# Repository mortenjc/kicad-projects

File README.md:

# kicad-projects
Files for schematics and PCB layout

## retroclock

This project relates to the DCF77 decoder project found here

https://github.com/mortenjc/dcf77

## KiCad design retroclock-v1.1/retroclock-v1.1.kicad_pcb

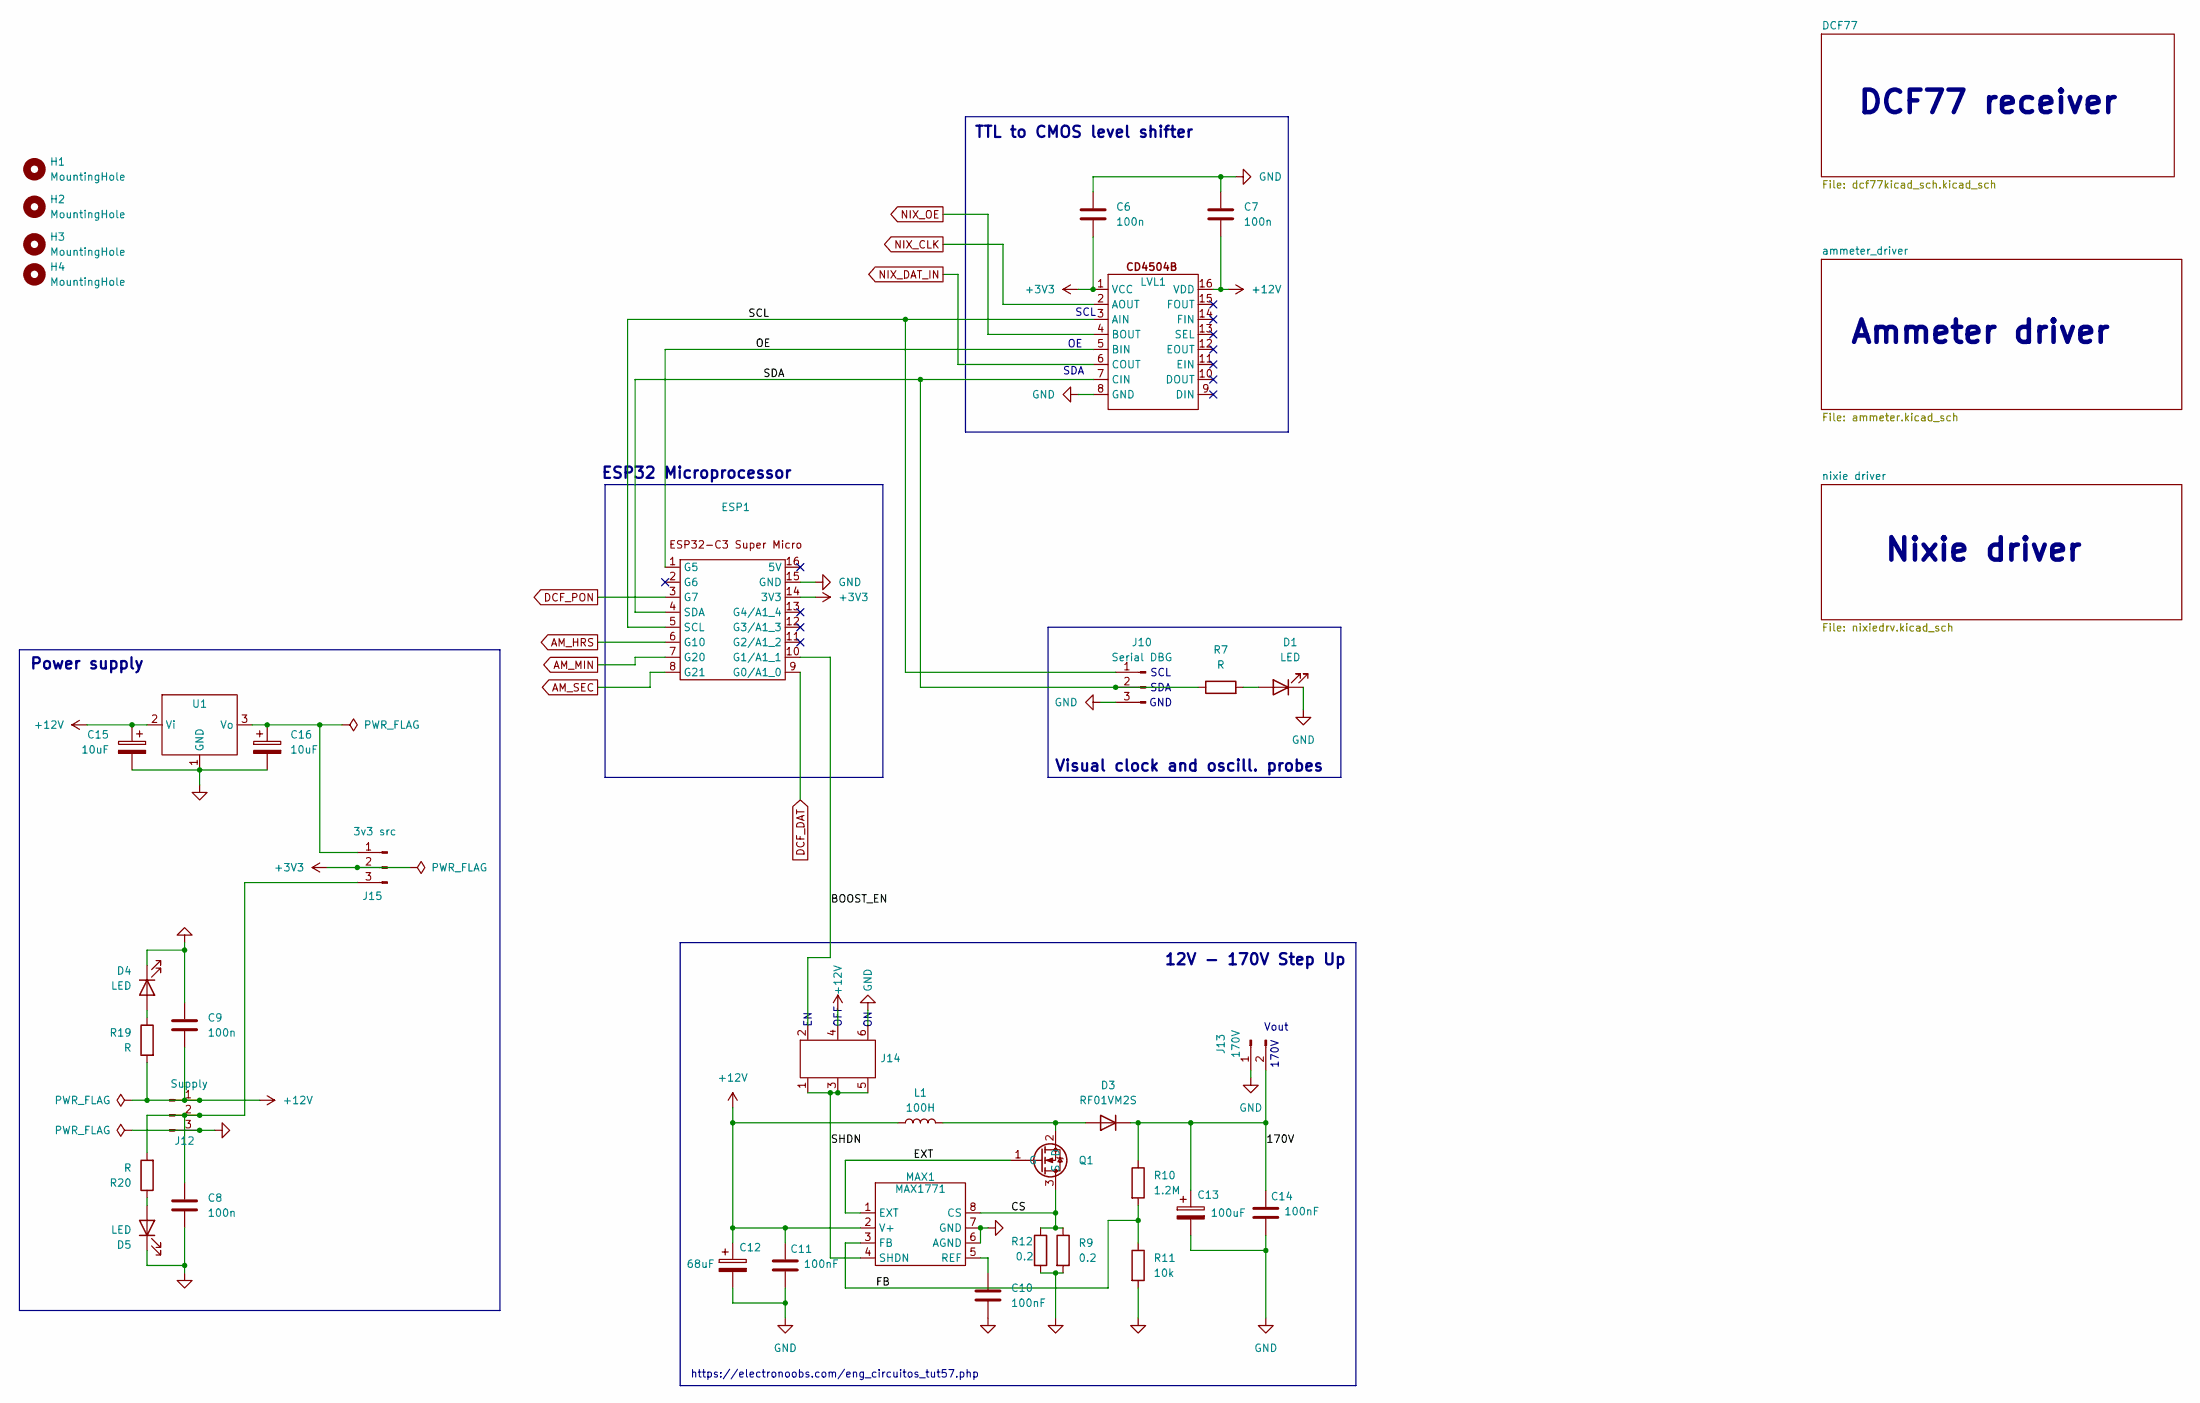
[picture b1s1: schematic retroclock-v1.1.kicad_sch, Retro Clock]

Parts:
C6, C8, C9: 100n; C_Disc_D3.4mm_W2.1mm_P2.50mm
C7: 100n; C_1206_3216Metric_Pad1.33x1.80mm_HandSolder
C10, C11: 100nF; C_Disc_D3.4mm_W2.1mm_P2.50mm
C12: 68uF; CP_Radial_D8.0mm_P3.80mm
C13: 100uF; CP_Radial_D10.0mm_P5.00mm
C14: 100nF; C_Rect_L18.0mm_W7.0mm_P15.00mm_FKS3_FKP3
C15, C16: 10uF; CP_Radial_D8.0mm_P3.80mm
D1, D4, D5: LED; LED_D3.0mm_Clear
D3: RF01VM2S; D_DO-15_P15.24mm_Horizontal
ESP1: ESP32 Header
H1, H2, H3, H4: MountingHole; MountingHole_2.2mm_M2_Pad
J10: Serial DBG; PinHeader_1x03_P2.54mm_Vertical
J12: Supply; Molex_KK-254_AE-6410-03A_1x03_P2.54mm_Vertical
J13: 170V; Molex_KK-254_AE-6410-02A_1x02_P2.54mm_Vertical
J14: Jumper 2.54 2x03
J15: 3v3 src; PinHeader_1x03_P2.54mm_Vertical
L1: 100H; L_Radial_D10.0mm_P5.00mm_Neosid_SD12k_style3
LVL1: SOIC-16_3.9x9.9mm_P1.27mm
MAX1: MAX1771; SOIC-8_3.9x4.9mm_P1.27mm
Q1: MOSFET
R7, R19, R20: R; R_Axial_DIN0204_L3.6mm_D1.6mm_P7.62mm_Horizontal
R9, R12: 0.2; R_Axial_DIN0204_L3.6mm_D1.6mm_P7.62mm_Horizontal
R10: 1.2M; R_Axial_DIN0204_L3.6mm_D1.6mm_P7.62mm_Horizontal
R11: 10k; R_Axial_DIN0204_L3.6mm_D1.6mm_P7.62mm_Horizontal
U1: HT7333

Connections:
+3V3: C6.2, ESP1.14 (3V3), J15.2, LVL1.1 (VCC); also elsewhere on the board
+12V: C7.1, C9.2, C11.1, C12.1, C15.1, J12.1, J14.4, L1.1, LVL1.16 (VDD), MAX1.2 (V+), R19.2, U1.2 (Vi); also elsewhere on the board
/170V: C13.1, C14.1, D3.1 (K), J13.2, R10.1
/BOOST_EN: ESP1.10 (G1/A1_1), J14.2
/CS: MAX1.8 (CS), Q1.3 (S), R9.1, R12.1
/EXT: MAX1.1 (EXT), Q1.1 (G)
/FB: MAX1.3 (FB), R10.2, R11.1
/OE: ESP1.1 (G5), LVL1.5 (BIN)
/SCL: ESP1.5 (SCL), J10.1, LVL1.3 (AIN)
/SDA: ESP1.4 (SDA), J10.2, LVL1.7 (CIN), R7.1
/SHDN: J14.1, J14.3, J14.5, MAX1.4 (SHDN)
AM_HRS: ESP1.6 (G10); also elsewhere on the board
AM_MIN: ESP1.7 (G20); also elsewhere on the board
AM_SEC: ESP1.8 (G21); also elsewhere on the board
DCF_DAT: ESP1.9 (G0/A1_0); also elsewhere on the board
DCF_PON: ESP1.3 (G7); also elsewhere on the board
GND: C6.1, C7.2, C8.2, C9.1, C10.2, C11.2, C12.2, C13.2, C14.2, C15.2, C16.2, D1.1 (K), D4.1 (K), D5.1 (K), ESP1.15 (GND), J10.3, J12.3, J13.1, J14.6, LVL1.8 (GND), MAX1.6 (AGND), MAX1.7 (GND), R9.2, R11.2, R12.2, U1.1 (GND); also elsewhere on the board
NIX_CLK: LVL1.2 (AOUT); also elsewhere on the board
NIX_DAT_IN: LVL1.6 (COUT); also elsewhere on the board
NIX_OE: LVL1.4 (BOUT); also elsewhere on the board
unnamed: D1.2 (A), R7.2
unnamed: D3.2 (A), L1.2, Q1.2 (D)
unnamed: D4.2 (A), R19.1
unnamed: D5.2 (A), R20.1
unnamed: C8.1, J12.2, J15.3, R20.2
unnamed: C16.1, J15.1, U1.3 (Vo)
unnamed: C10.1, MAX1.5 (REF)

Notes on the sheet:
https://electronoobs.com/eng_circuitos_tut57.php
ESP32 Microprocessor
Nixie driver
GND
SCL
OFF
Vout
Power supply
170V
Visual clock and oscill. probes
SDA
12V - 170V Step Up
DCF77 receiver
TTL to CMOS level shifter
Ammeter driver

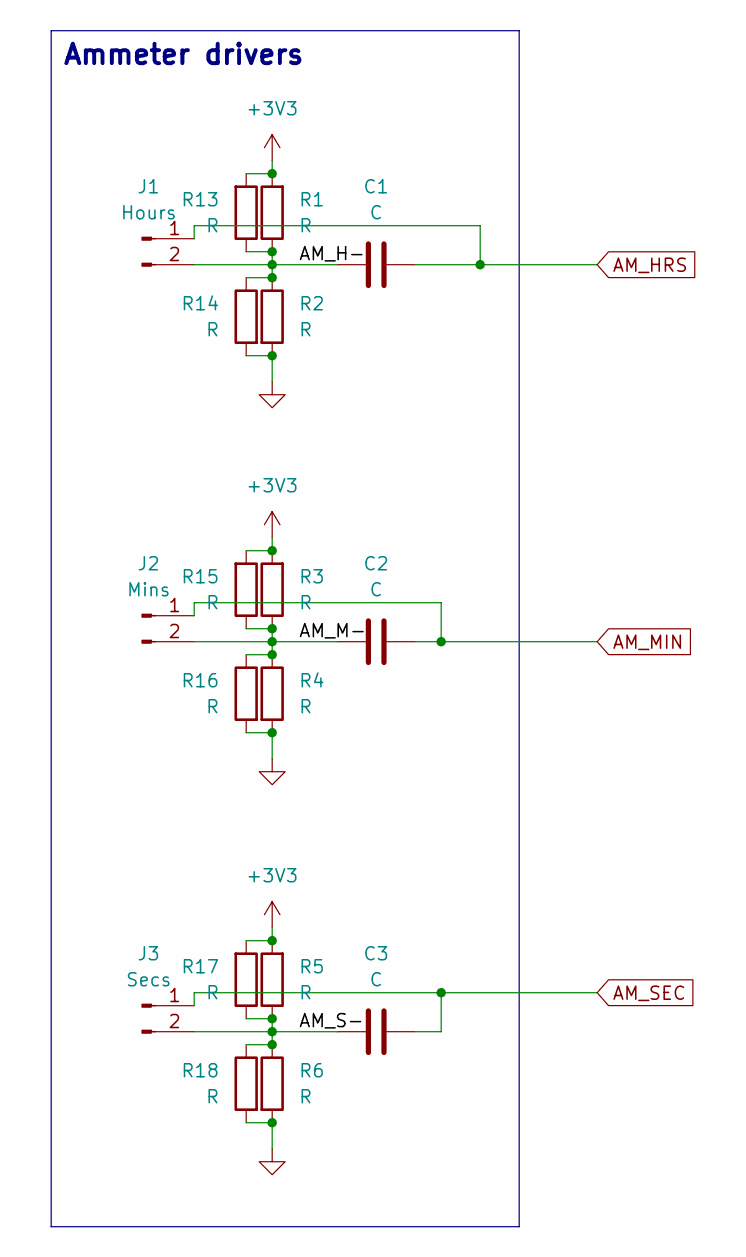
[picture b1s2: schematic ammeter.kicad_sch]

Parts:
C1, C2, C3: C; C_Axial_L19.0mm_D7.5mm_P25.00mm_Horizontal
J1: Hours; Molex_KK-254_AE-6410-02A_1x02_P2.54mm_Vertical
J2: Mins; Molex_KK-254_AE-6410-02A_1x02_P2.54mm_Vertical
J3: Secs; Molex_KK-254_AE-6410-02A_1x02_P2.54mm_Vertical
R1, R2, R3, R4, R5, R6, R13, R14, R15, R16, R17, R18: R; R_Axial_DIN0204_L3.6mm_D1.6mm_P7.62mm_Horizontal

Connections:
+3V3: R1.2, R3.2, R5.2, R13.2, R15.2, R17.2; also elsewhere on the board
/ammeter_driver/AM_H-: C1.2, J1.2, R1.1, R2.1, R13.1, R14.1
/ammeter_driver/AM_M-: C2.2, J2.2, R3.1, R4.1, R15.1, R16.1
/ammeter_driver/AM_S-: C3.2, J3.2, R5.1, R6.1, R17.1, R18.1
AM_HRS: C1.1, J1.1; also elsewhere on the board
AM_MIN: C2.1, J2.1; also elsewhere on the board
AM_SEC: C3.1, J3.1; also elsewhere on the board
GND: R2.2, R4.2, R6.2, R14.2, R16.2, R18.2; also elsewhere on the board

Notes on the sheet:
Ammeter drivers

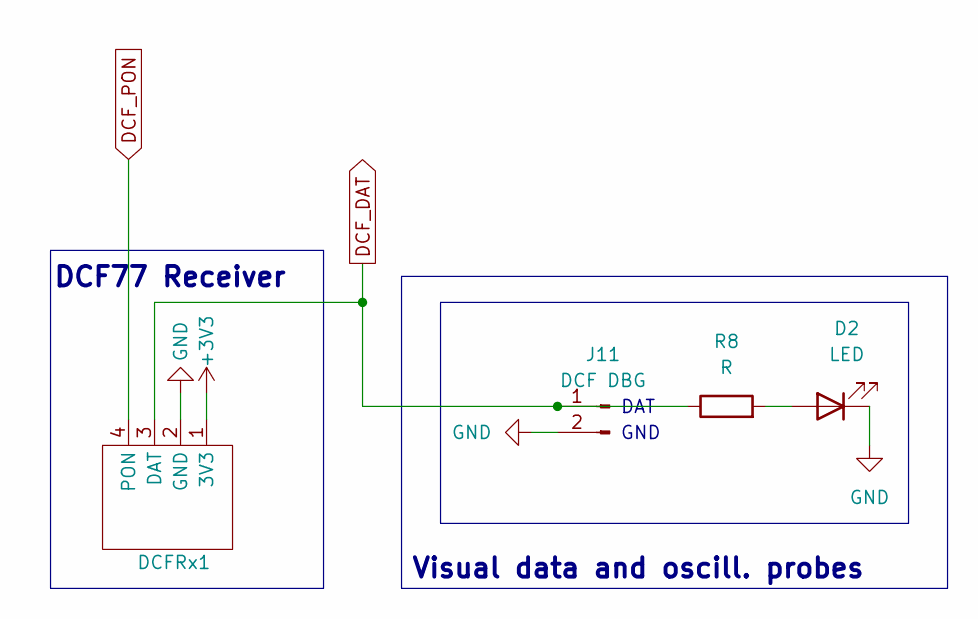
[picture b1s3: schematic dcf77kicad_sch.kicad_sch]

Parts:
D2: LED; LED_D3.0mm_Clear
DCFRx1: DCF77Rx_A
J11: DCF DBG; Molex_KK-254_AE-6410-02A_1x02_P2.54mm_Vertical
R8: R; R_Axial_DIN0204_L3.6mm_D1.6mm_P7.62mm_Horizontal

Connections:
+3V3: DCFRx1.1 (3V3); also elsewhere on the board
DCF_DAT: DCFRx1.3 (DAT), J11.1, R8.1; also elsewhere on the board
DCF_PON: DCFRx1.4 (PON); also elsewhere on the board
GND: D2.1 (K), DCFRx1.2 (GND), J11.2; also elsewhere on the board
unnamed: D2.2 (A), R8.2

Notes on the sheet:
GND
DAT
DCF77 Receiver
Visual data and oscill. probes

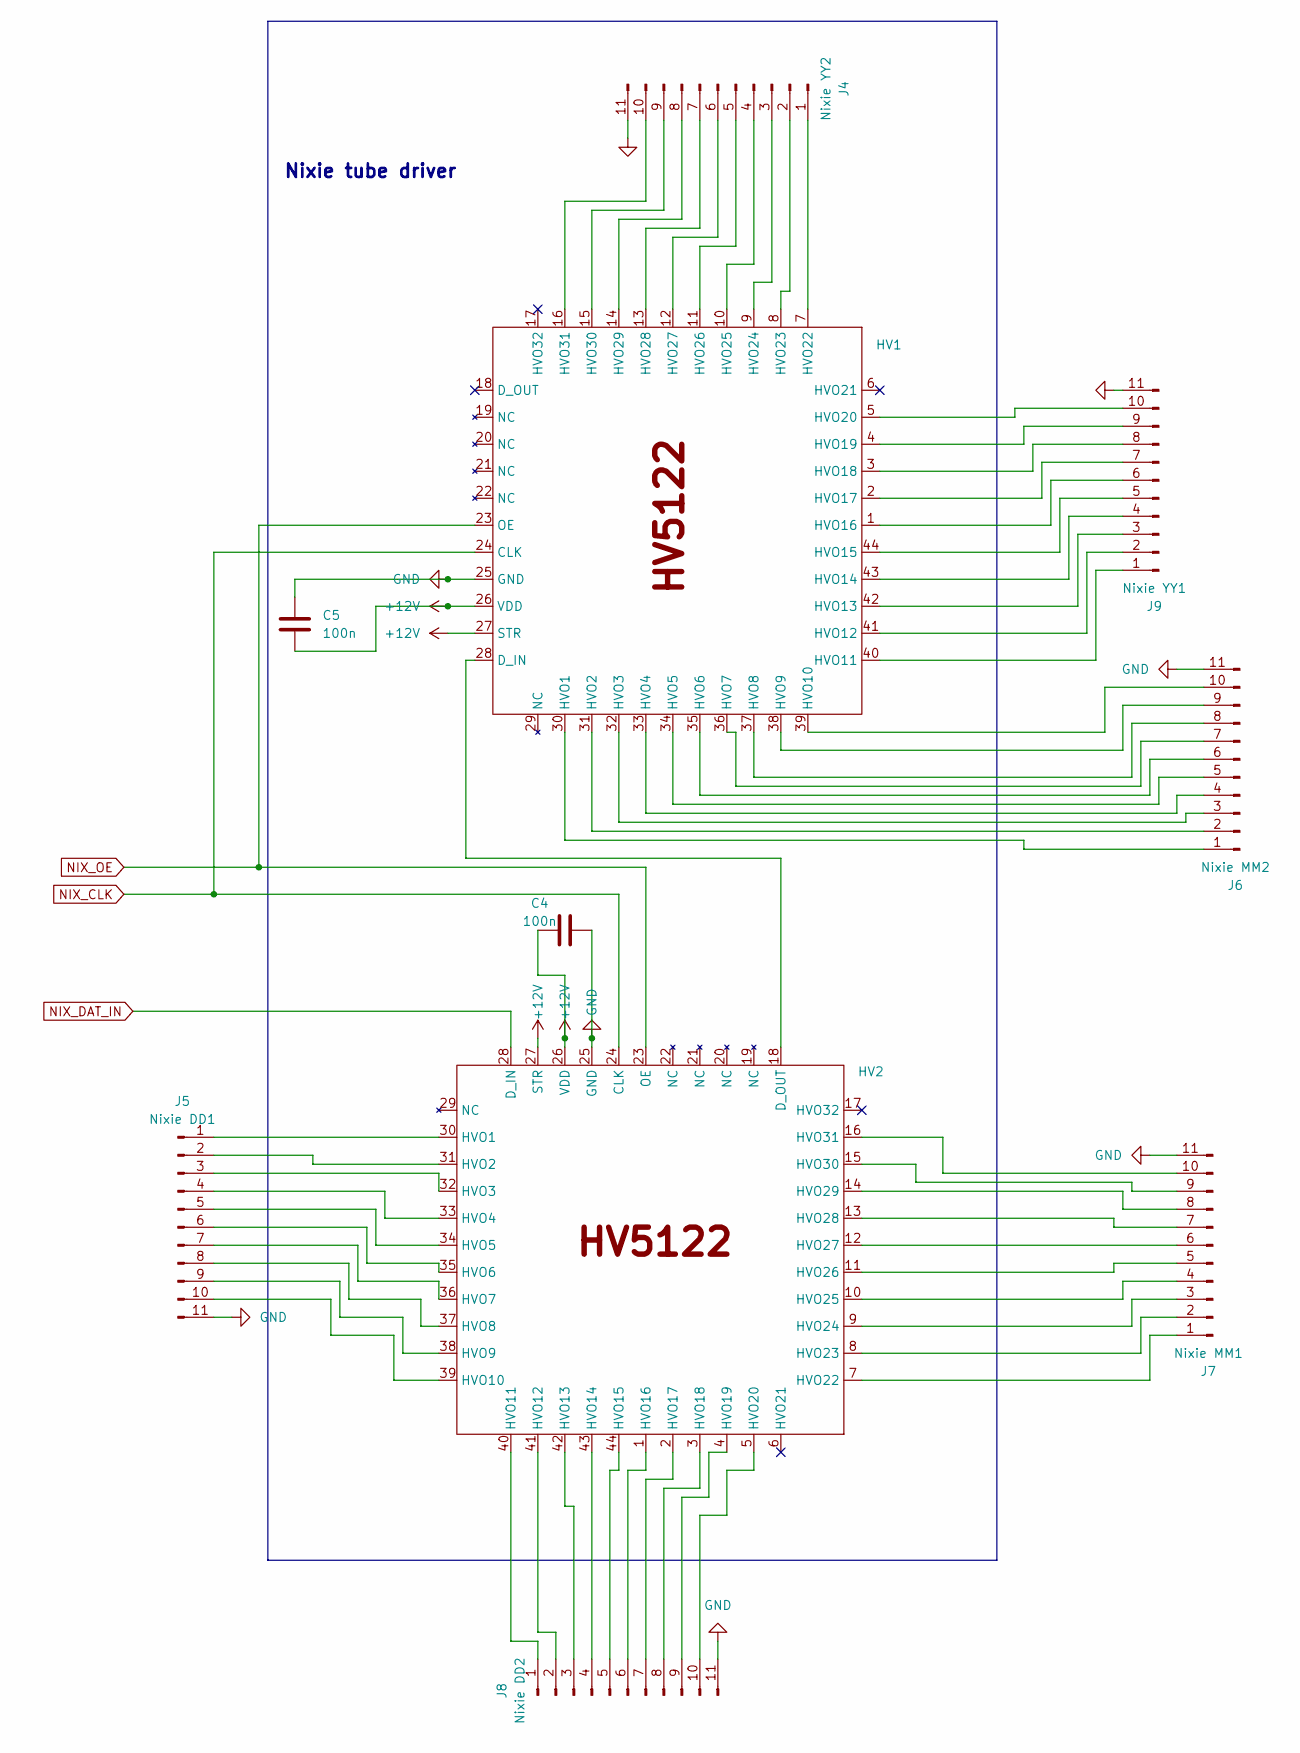
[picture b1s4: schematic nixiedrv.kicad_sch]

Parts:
C4: 100n; C_Disc_D3.4mm_W2.1mm_P2.50mm
C5: 100n; C_1206_3216Metric_Pad1.33x1.80mm_HandSolder
HV1, HV2: PLCC44 MillMaxMfg 940
J4: Nixie YY2; PinHeader_2x07_P2.54mm_Vertical
J5: Nixie DD1; PinHeader_2x07_P2.54mm_Vertical
J6: Nixie MM2; PinHeader_2x07_P2.54mm_Vertical
J7: Nixie MM1; PinHeader_2x07_P2.54mm_Vertical
J8: Nixie DD2; PinHeader_2x07_P2.54mm_Vertical
J9: Nixie YY1; PinHeader_2x07_P2.54mm_Vertical

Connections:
+12V: C4.1, C5.1, HV1.26 (VDD), HV1.27 (STR), HV2.26 (VDD), HV2.27 (STR); also elsewhere on the board
GND: C4.2, C5.2, HV1.25 (GND), HV2.25 (GND), J4.11, J5.11, J6.11, J7.11, J8.11, J9.11; also elsewhere on the board
NIX_CLK: HV1.24 (CLK), HV2.24 (CLK); also elsewhere on the board
NIX_DAT_IN: HV2.28 (D_IN); also elsewhere on the board
NIX_OE: HV1.23 (OE), HV2.23 (OE); also elsewhere on the board
unnamed: HV1.28 (D_IN), HV2.18 (D_OUT)
unnamed: HV1.30 (HVO1), J6.1
unnamed: HV1.31 (HVO2), J6.2
unnamed: HV1.32 (HVO3), J6.3
unnamed: HV1.33 (HVO4), J6.4
unnamed: HV1.34 (HVO5), J6.5
unnamed: HV1.35 (HVO6), J6.6
unnamed: HV1.36 (HVO7), J6.7
unnamed: HV1.37 (HVO8), J6.8
unnamed: HV1.38 (HVO9), J6.9
unnamed: HV1.39 (HVO10), J6.10
unnamed: HV1.40 (HVO11), J9.1
unnamed: HV1.41 (HVO12), J9.2
unnamed: HV1.42 (HVO13), J9.3
unnamed: HV1.43 (HVO14), J9.4
unnamed: HV1.44 (HVO15), J9.5
unnamed: HV1.1 (HVO16), J9.6
unnamed: HV1.2 (HVO17), J9.7
unnamed: HV1.3 (HVO18), J9.8
unnamed: HV1.4 (HVO19), J9.9
unnamed: HV1.5 (HVO20), J9.10
unnamed: HV1.7 (HVO22), J4.1
unnamed: HV1.8 (HVO23), J4.2
unnamed: HV1.9 (HVO24), J4.3
unnamed: HV1.10 (HVO25), J4.4
unnamed: HV1.11 (HVO26), J4.5
unnamed: HV1.12 (HVO27), J4.6
unnamed: HV1.13 (HVO28), J4.7
unnamed: HV1.14 (HVO29), J4.8
unnamed: HV1.15 (HVO30), J4.9
unnamed: HV1.16 (HVO31), J4.10
unnamed: HV2.30 (HVO1), J5.1
unnamed: HV2.31 (HVO2), J5.2
unnamed: HV2.32 (HVO3), J5.3
unnamed: HV2.33 (HVO4), J5.4
unnamed: HV2.34 (HVO5), J5.5
unnamed: HV2.35 (HVO6), J5.6
unnamed: HV2.36 (HVO7), J5.7
unnamed: HV2.37 (HVO8), J5.8
unnamed: HV2.38 (HVO9), J5.9
unnamed: HV2.39 (HVO10), J5.10
unnamed: HV2.40 (HVO11), J8.1
unnamed: HV2.41 (HVO12), J8.2
unnamed: HV2.42 (HVO13), J8.3
unnamed: HV2.43 (HVO14), J8.4
unnamed: HV2.44 (HVO15), J8.5
unnamed: HV2.1 (HVO16), J8.6
unnamed: HV2.2 (HVO17), J8.7
unnamed: HV2.3 (HVO18), J8.8
unnamed: HV2.4 (HVO19), J8.9
unnamed: HV2.5 (HVO20), J8.10
unnamed: HV2.7 (HVO22), J7.1
unnamed: HV2.8 (HVO23), J7.2
unnamed: HV2.9 (HVO24), J7.3
unnamed: HV2.10 (HVO25), J7.4
unnamed: HV2.11 (HVO26), J7.5
unnamed: HV2.12 (HVO27), J7.6
unnamed: HV2.13 (HVO28), J7.7
unnamed: HV2.14 (HVO29), J7.8
unnamed: HV2.15 (HVO30), J7.9
unnamed: HV2.16 (HVO31), J7.10

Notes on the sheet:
Nixie tube driver

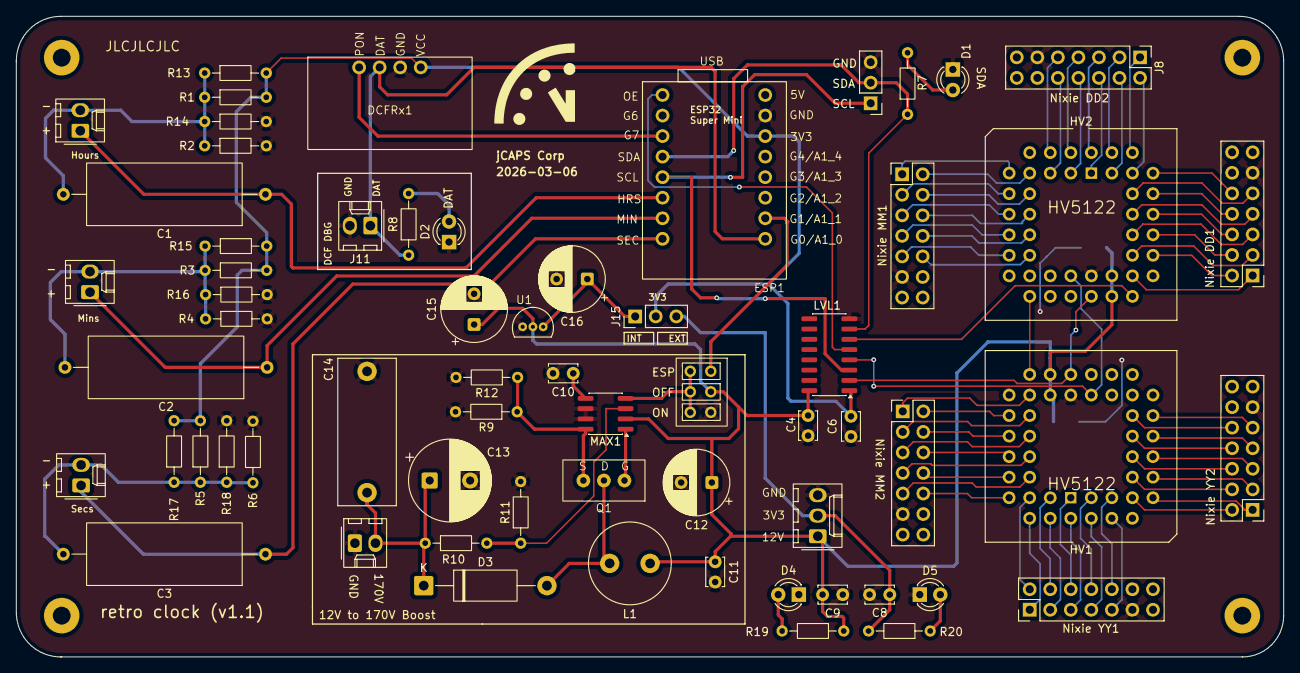
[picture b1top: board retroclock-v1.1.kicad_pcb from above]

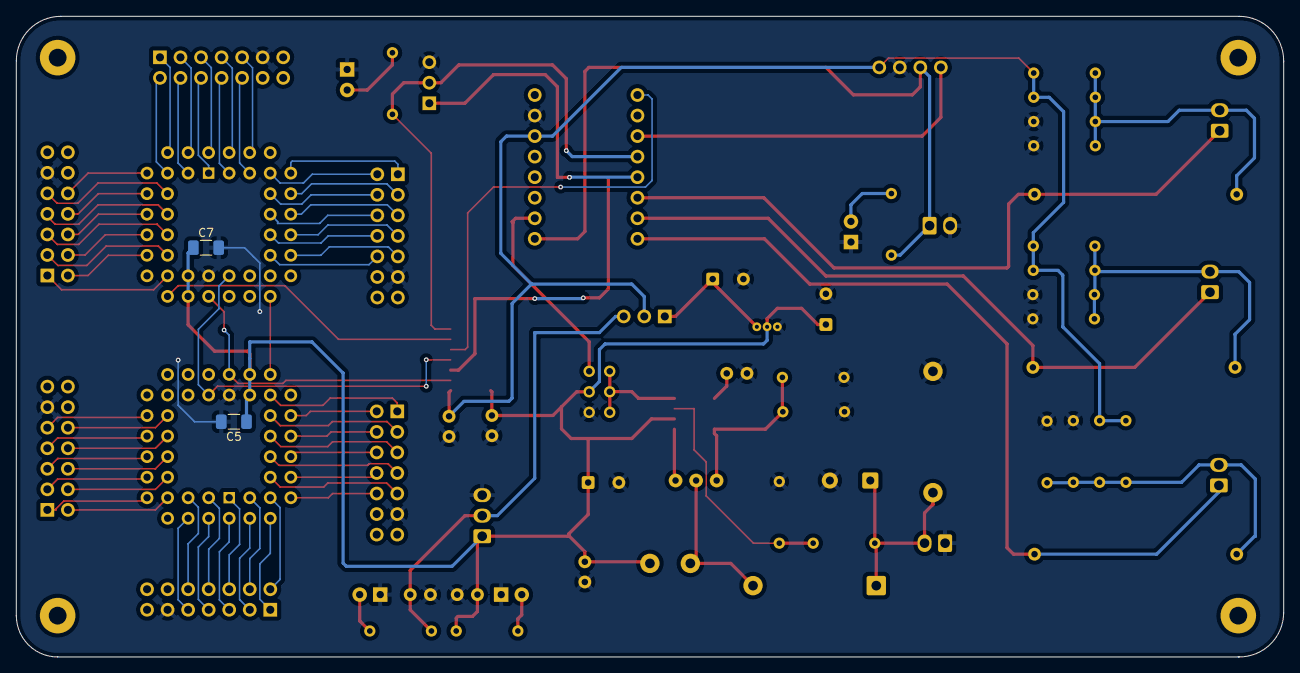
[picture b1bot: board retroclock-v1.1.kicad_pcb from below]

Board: 2 copper layers, 156.7 x 79.2 mm, 69 parts (2 on the bottom side), 92 nets.

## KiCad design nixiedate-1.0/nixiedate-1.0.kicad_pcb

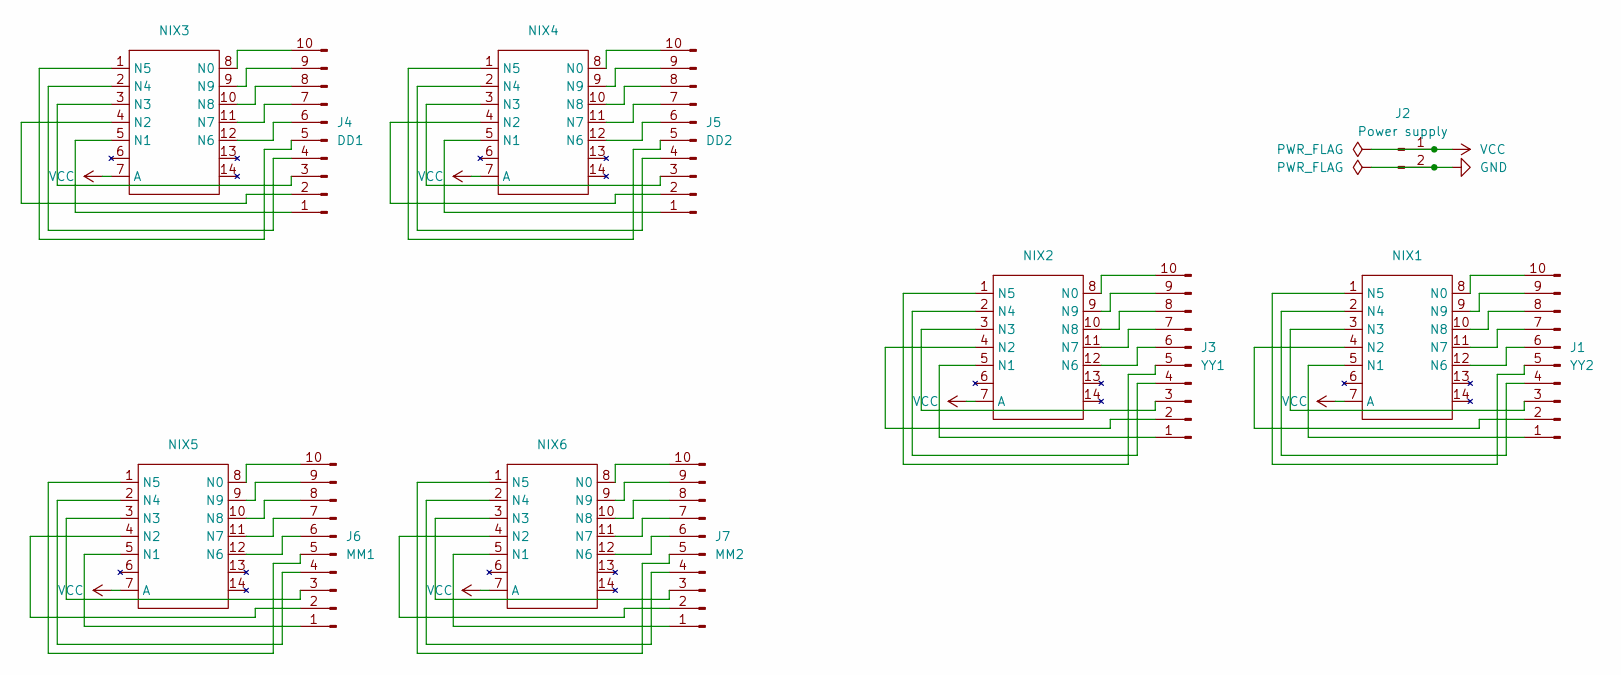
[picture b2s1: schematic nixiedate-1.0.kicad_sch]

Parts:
J1: YY2; PinHeader_1x10_P2.54mm_Vertical
J2: Power supply; PinHeader_1x02_P2.54mm_Vertical
J3: YY1; PinHeader_1x10_P2.54mm_Vertical
J4: DD1; PinHeader_1x10_P2.54mm_Vertical
J5: DD2; PinHeader_1x10_P2.54mm_Vertical
J6: MM1; PinHeader_1x10_P2.54mm_Vertical
J7: MM2; PinHeader_1x10_P2.54mm_Vertical
NIX1, NIX2, NIX3, NIX4, NIX5, NIX6: JAN8422

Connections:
GND: J2.2
unnamed: J1.1, NIX1.5 (N1)
unnamed: J1.2, NIX1.4 (N2)
unnamed: J1.3, NIX1.3 (N3)
unnamed: J1.4, NIX1.2 (N4)
unnamed: J1.5, NIX1.1 (N5)
unnamed: J1.6, NIX1.12 (N6)
unnamed: J1.7, NIX1.11 (N7)
unnamed: J1.8, NIX1.10 (N8)
unnamed: J1.9, NIX1.9 (N9)
unnamed: J1.10, NIX1.8 (N0)
unnamed: J3.1, NIX2.5 (N1)
unnamed: J3.2, NIX2.4 (N2)
unnamed: J3.3, NIX2.3 (N3)
unnamed: J3.4, NIX2.2 (N4)
unnamed: J3.5, NIX2.1 (N5)
unnamed: J3.6, NIX2.12 (N6)
unnamed: J3.7, NIX2.11 (N7)
unnamed: J3.8, NIX2.10 (N8)
unnamed: J3.9, NIX2.9 (N9)
unnamed: J3.10, NIX2.8 (N0)
unnamed: J4.1, NIX3.5 (N1)
unnamed: J4.2, NIX3.4 (N2)
unnamed: J4.3, NIX3.3 (N3)
unnamed: J4.4, NIX3.2 (N4)
unnamed: J4.5, NIX3.1 (N5)
unnamed: J4.6, NIX3.12 (N6)
unnamed: J4.7, NIX3.11 (N7)
unnamed: J4.8, NIX3.10 (N8)
unnamed: J4.9, NIX3.9 (N9)
unnamed: J4.10, NIX3.8 (N0)
unnamed: J5.1, NIX4.5 (N1)
unnamed: J5.2, NIX4.4 (N2)
unnamed: J5.3, NIX4.3 (N3)
unnamed: J5.4, NIX4.2 (N4)
unnamed: J5.5, NIX4.1 (N5)
unnamed: J5.6, NIX4.12 (N6)
unnamed: J5.7, NIX4.11 (N7)
unnamed: J5.8, NIX4.10 (N8)
unnamed: J5.9, NIX4.9 (N9)
unnamed: J5.10, NIX4.8 (N0)
unnamed: J6.1, NIX5.5 (N1)
unnamed: J6.2, NIX5.4 (N2)
unnamed: J6.3, NIX5.3 (N3)
unnamed: J6.4, NIX5.2 (N4)
unnamed: J6.5, NIX5.1 (N5)
unnamed: J6.6, NIX5.12 (N6)
unnamed: J6.7, NIX5.11 (N7)
unnamed: J6.8, NIX5.10 (N8)
unnamed: J6.9, NIX5.9 (N9)
unnamed: J6.10, NIX5.8 (N0)
unnamed: J7.1, NIX6.5 (N1)
unnamed: J7.2, NIX6.4 (N2)
unnamed: J7.3, NIX6.3 (N3)
unnamed: J7.4, NIX6.2 (N4)
unnamed: J7.5, NIX6.1 (N5)
unnamed: J7.6, NIX6.12 (N6)
unnamed: J7.7, NIX6.11 (N7)
unnamed: J7.8, NIX6.10 (N8)
unnamed: J7.9, NIX6.9 (N9)
unnamed: J7.10, NIX6.8 (N0)
VCC: J2.1, NIX1.7 (A), NIX2.7 (A), NIX3.7 (A), NIX4.7 (A), NIX5.7 (A), NIX6.7 (A)

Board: 4 copper layers, 13 parts (7 on the bottom side), 61 nets, no tracks yet.

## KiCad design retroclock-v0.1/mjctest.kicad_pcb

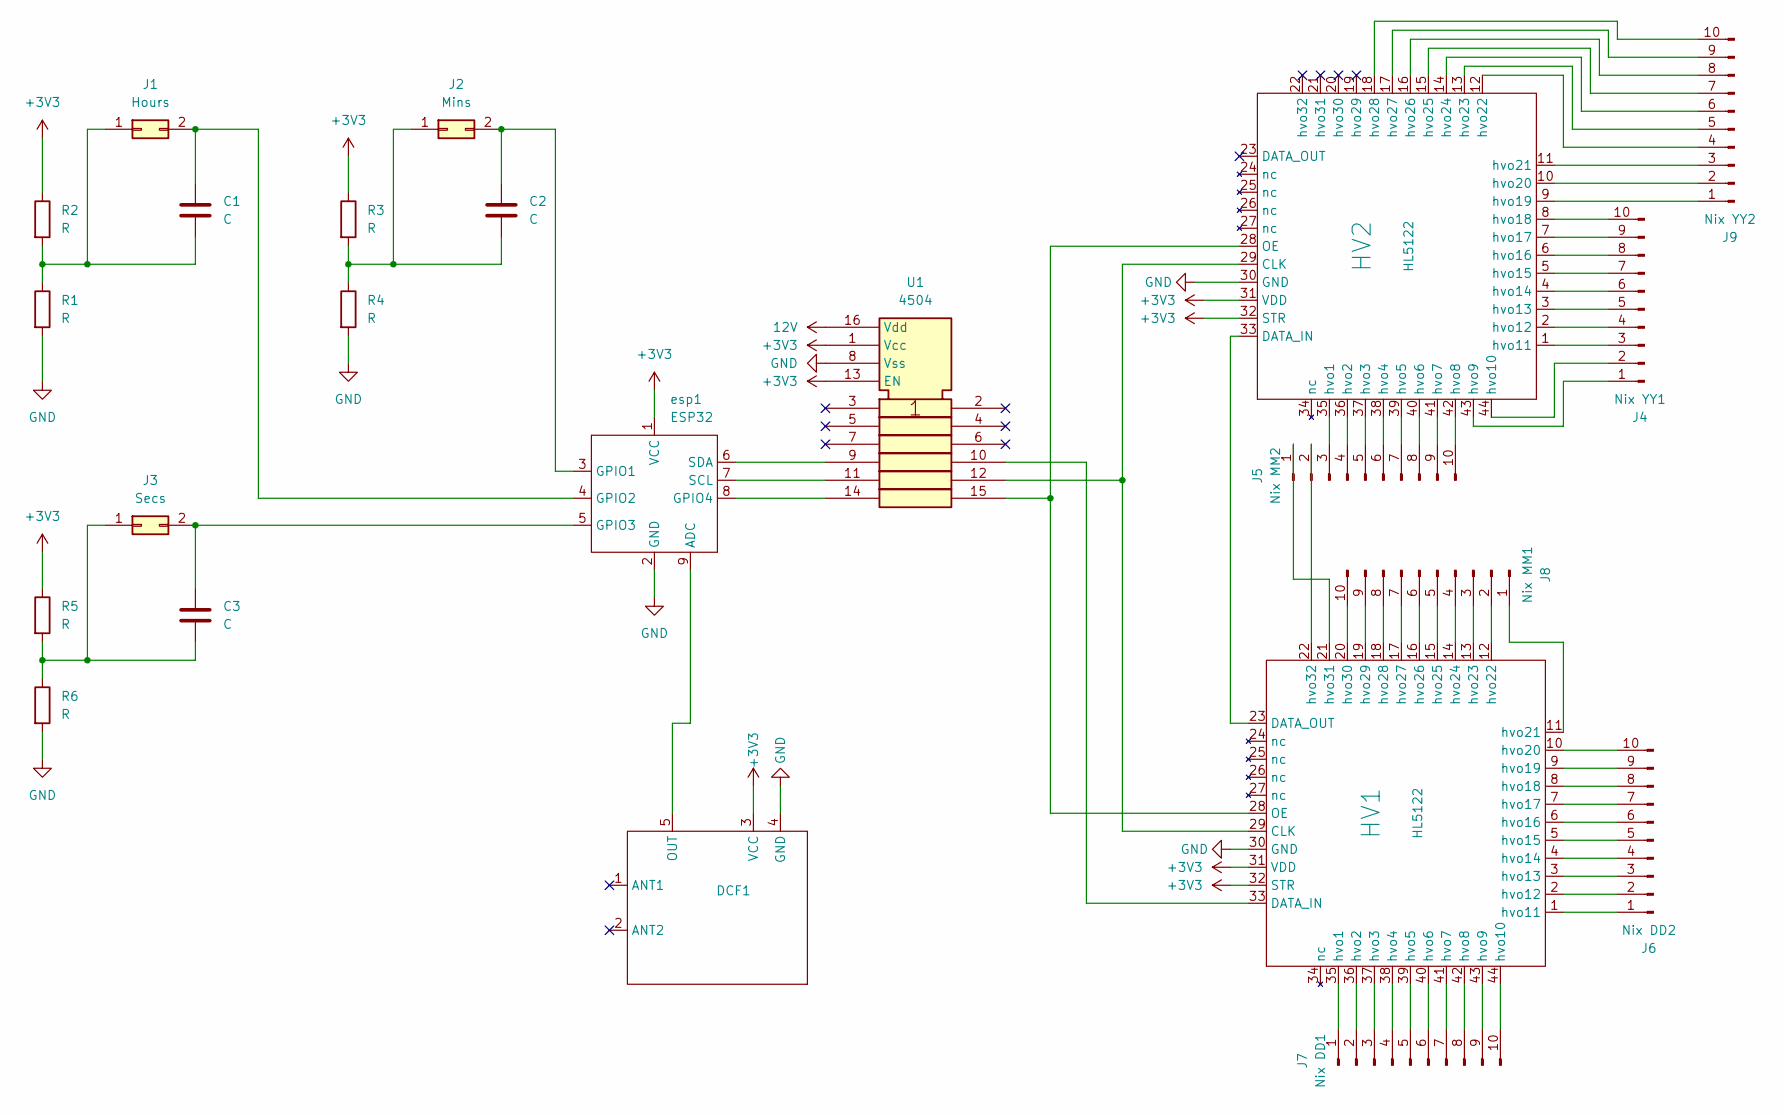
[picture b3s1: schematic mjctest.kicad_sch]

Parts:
C1, C2, C3: C; CP_Axial_L18.0mm_D6.5mm_P25.00mm_Horizontal
DCF1: DCF77
HV1, HV2: HL5122; HV5122
J1: Hours; PinHeader_1x02_P1.00mm_Horizontal
J2: Mins; PinHeader_1x02_P1.00mm_Horizontal
J3: Secs; PinHeader_1x02_P1.00mm_Horizontal
J4: Nix YY1; PinHeader_1x10_P1.00mm_Vertical
J5: Nix MM2; PinHeader_1x10_P1.00mm_Vertical
J6: Nix DD2; PinHeader_1x10_P1.00mm_Vertical
J7: Nix DD1; PinHeader_1x10_P1.00mm_Vertical
J8: Nix MM1; PinHeader_1x10_P1.00mm_Vertical
J9: Nix YY2; PinHeader_1x10_P1.00mm_Vertical
R1, R2, R3, R4, R5, R6: R; R_Axial_DIN0204_L3.6mm_D1.6mm_P7.62mm_Horizontal
U1: 4504; CD4504B
esp1: ESP32; WEMOS_C3_mini

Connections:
12V: U1.16 (Vdd)
+3V3: DCF1.3 (VCC), HV1.31 (VDD), HV1.32 (STR), HV2.31 (VDD), HV2.32 (STR), R2.1, R3.1, R5.1, U1.1 (Vcc), U1.13 (EN), esp1.1 (VCC)
GND: DCF1.4 (GND), HV1.30 (GND), HV2.30 (GND), R1.2, R4.2, R6.2, U1.8 (Vss), esp1.2 (GND)
unnamed: DCF1.5 (OUT), esp1.9 (ADC)
unnamed: HV1.29 (CLK), HV2.29 (CLK), U1.12
unnamed: HV1.33 (DATA_IN), U1.10
unnamed: HV1.23 (DATA_OUT), HV2.33 (DATA_IN)
unnamed: HV1.28 (OE), HV2.28 (OE), U1.15
unnamed: HV1.35 (hvo1), J7.1
unnamed: HV1.36 (hvo2), J7.2
unnamed: HV1.37 (hvo3), J7.3
unnamed: HV1.38 (hvo4), J7.4
unnamed: HV1.39 (hvo5), J7.5
unnamed: HV1.40 (hvo6), J7.6
unnamed: HV1.41 (hvo7), J7.7
unnamed: HV1.42 (hvo8), J7.8
unnamed: HV1.43 (hvo9), J7.9
unnamed: HV1.44 (hvo10), J7.10
unnamed: HV1.1 (hvo11), J6.1
unnamed: HV1.2 (hvo12), J6.2
unnamed: HV1.3 (hvo13), J6.3
unnamed: HV1.4 (hvo14), J6.4
unnamed: HV1.5 (hvo15), J6.5
unnamed: HV1.6 (hvo16), J6.6
unnamed: HV1.7 (hvo17), J6.7
unnamed: HV1.8 (hvo18), J6.8
unnamed: HV1.9 (hvo19), J6.9
unnamed: HV1.10 (hvo20), J6.10
unnamed: HV1.11 (hvo21), J8.1
unnamed: HV1.12 (hvo22), J8.2
unnamed: HV1.13 (hvo23), J8.3
unnamed: HV1.14 (hvo24), J8.4
unnamed: HV1.15 (hvo25), J8.5
unnamed: HV1.16 (hvo26), J8.6
unnamed: HV1.17 (hvo27), J8.7
unnamed: HV1.18 (hvo28), J8.8
unnamed: HV1.19 (hvo29), J8.9
unnamed: HV1.20 (hvo30), J8.10
unnamed: HV1.21 (hvo31), J5.1
unnamed: HV1.22 (hvo32), J5.2
unnamed: HV2.35 (hvo1), J5.3
unnamed: HV2.36 (hvo2), J5.4
unnamed: HV2.37 (hvo3), J5.5
unnamed: HV2.38 (hvo4), J5.6
unnamed: HV2.39 (hvo5), J5.7
unnamed: HV2.40 (hvo6), J5.8
unnamed: HV2.41 (hvo7), J5.9
unnamed: HV2.42 (hvo8), J5.10
unnamed: HV2.43 (hvo9), J4.1
unnamed: HV2.44 (hvo10), J4.2
unnamed: HV2.1 (hvo11), J4.3
unnamed: HV2.2 (hvo12), J4.4
unnamed: HV2.3 (hvo13), J4.5
unnamed: HV2.4 (hvo14), J4.6
unnamed: HV2.5 (hvo15), J4.7
unnamed: HV2.6 (hvo16), J4.8
unnamed: HV2.7 (hvo17), J4.9
unnamed: HV2.8 (hvo18), J4.10
unnamed: HV2.9 (hvo19), J9.1
unnamed: HV2.10 (hvo20), J9.2
unnamed: HV2.11 (hvo21), J9.3
unnamed: HV2.12 (hvo22), J9.4
unnamed: HV2.13 (hvo23), J9.5
unnamed: HV2.14 (hvo24), J9.6
unnamed: HV2.15 (hvo25), J9.7
unnamed: HV2.16 (hvo26), J9.8
unnamed: HV2.17 (hvo27), J9.9
unnamed: HV2.18 (hvo28), J9.10
unnamed: C1.2, J1.1, R1.1, R2.2
unnamed: C1.1, J1.2, esp1.4 (GPIO2)
unnamed: C2.2, J2.1, R3.2, R4.1
unnamed: C2.1, J2.2, esp1.3 (GPIO1)
unnamed: C3.2, J3.1, R5.2, R6.1
unnamed: C3.1, J3.2, esp1.5 (GPIO3)
unnamed: U1.14, esp1.8 (GPIO4)
unnamed: U1.11, esp1.7 (SCL)
unnamed: U1.9, esp1.6 (SDA)

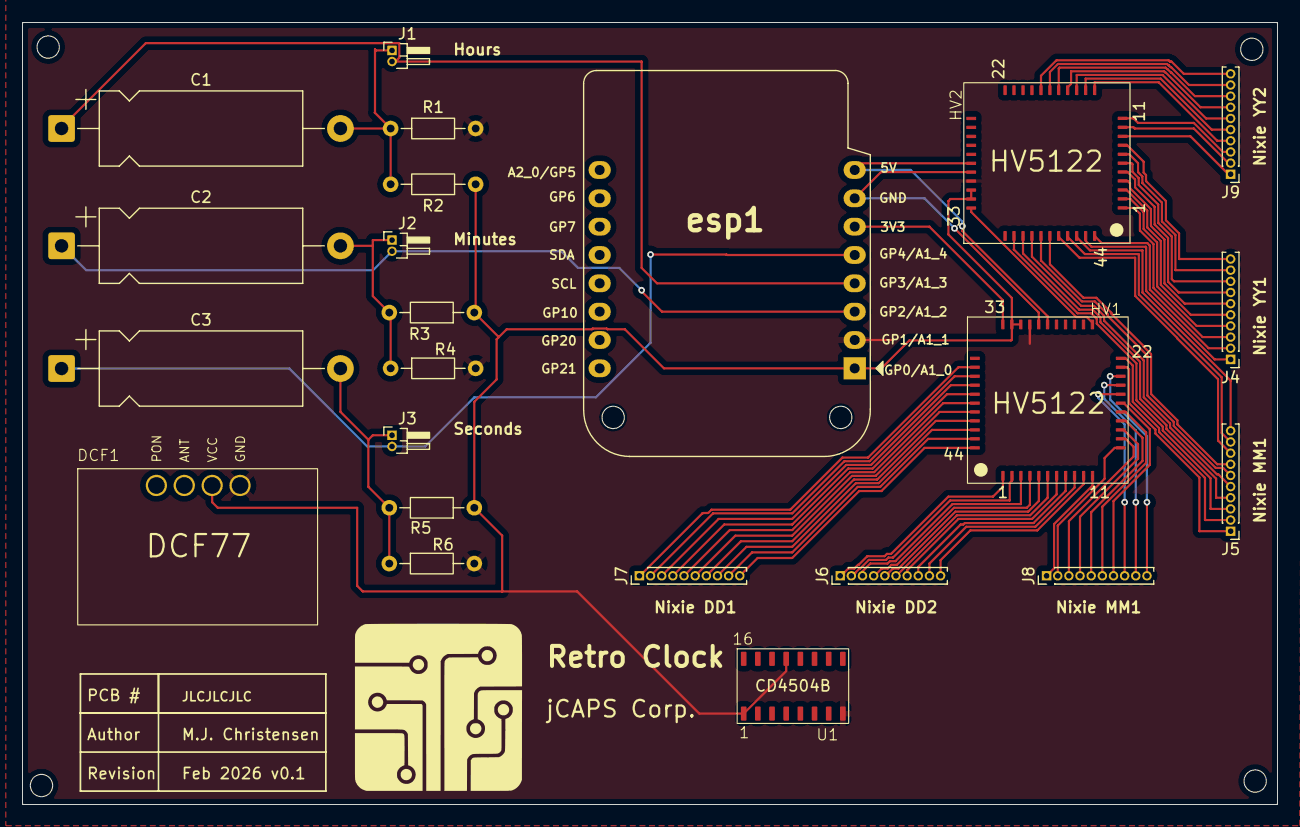
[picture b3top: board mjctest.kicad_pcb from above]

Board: 4 copper layers, 112.5 x 70.1 mm, 23 parts (0 on the bottom side), 75 nets.

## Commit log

2026-02-17 migrated first project from random location
2026-02-17 adding directory for the next iteration
2026-02-18 added some footprints
2026-02-18 finished routing, no errors
2026-03-08 retroclock 1.1 sent to JLCPCB!
